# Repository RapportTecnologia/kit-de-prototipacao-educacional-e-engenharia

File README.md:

# Kit Educacional e Prototipação Rapport

* **Versão atual:** 0.6

---

## Visão geral

Este repositório contém o projeto do **Kit Educacional e de Prototipação** da Rapport (Kit Educacional e Prototipação Rapport - KEPR), incluindo a documentação do barramento/modularidade (UCE) e os arquivos de CAD eletrônico em KiCad.

O KEPR é um ecossistema de hardware para **prototipação e aprendizagem** em sistemas embarcados e IoT: uma base modular que permite trocar o microcontrolador sem “quebrar” o restante do projeto, além de integrar **módulos de rede e wireless** (WiFi, Bluetooth e outros) quando essas interfaces não estão disponíveis nativamente no módulo principal.

A proposta é reduzir atrito no desenvolvimento (e no estudo) de firmware e hardware, organizando um padrão de conexão e expansão para acelerar testes, validações e iterações. O projeto busca compatibilidade com famílias como **STM32**, **ESP32**, **AVR (ATtiny/ATmega)** e outros fabricantes.

Este projeto nasce inicialmente com fins **educacionais** (estudos e evolução técnica de Carlos Delfino) e **pode vir a se tornar comercial** no futuro. Ainda assim, o projeto permanece sob a mesma licença para que outras pessoas e empresas possam **usar, adaptar e redistribuir** da forma que desejarem.

**Licença:** Creative Commons **CC BY 4.0** (atribuição). Se você quer colaborar, você pode:

- propor melhorias na arquitetura do barramento e dos módulos;
- revisar esquemáticos/footprints e sugerir boas práticas de layout;
- abrir issues com dúvidas, críticas e ideias;
- enviar PRs com correções, melhorias e novos módulos.

---

## Documentação

- **UCE (placa / barramento):** `UCE_BOARD.md`
- **Changelog:** `CHANGELOG.md`

---

## Projeto KiCad

O projeto principal atualmente está em:

- `kicad/KEPR/`

---

## Repositório Git (origem)

- `git@github.com:RapportTecnologia/kit-de-prototipacao-educacional-e-engenharia.git`

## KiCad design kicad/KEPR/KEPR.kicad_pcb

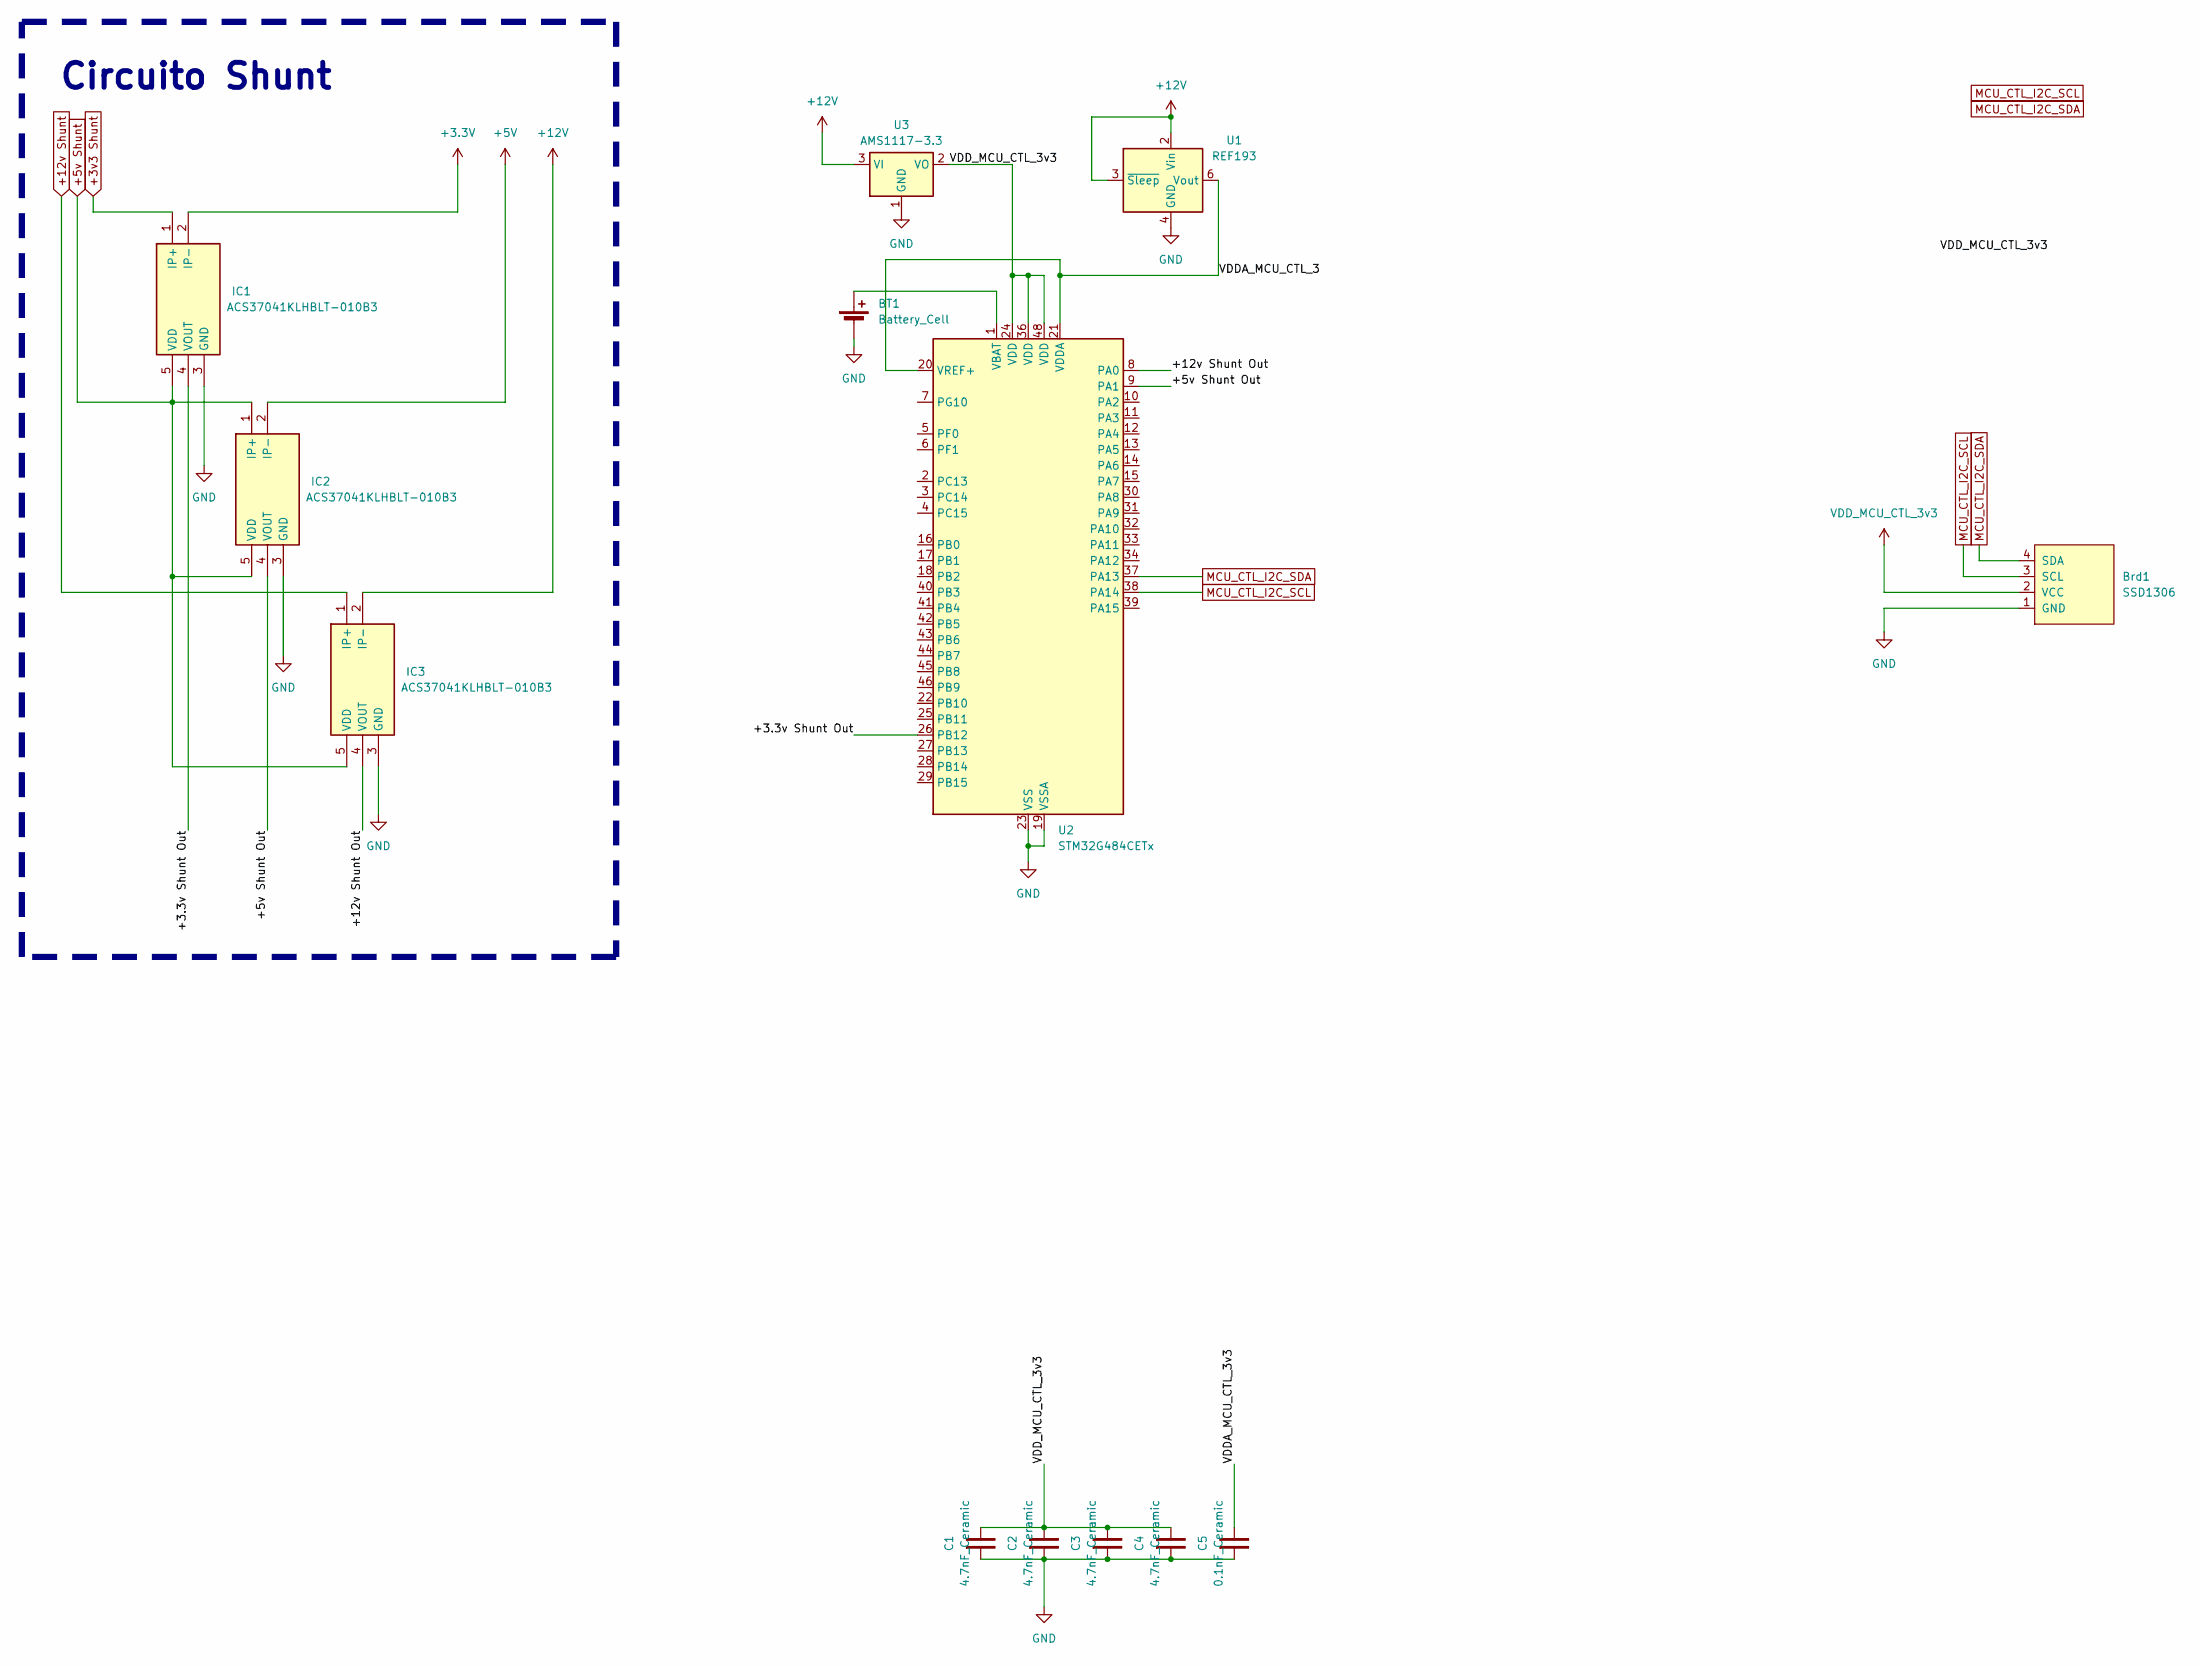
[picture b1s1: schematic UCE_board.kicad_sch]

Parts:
BT1: Battery_Cell; BatteryHolder_Multicomp_BC-2001_1x2032
Brd1: SSD1306; 128x64OLED
C1, C2, C3, C4: 4.7nF_Ceramic; C_0805_2012Metric
C5: 0.1nF_Ceramic; C_0805_2012Metric
IC1, IC2, IC3: ACS37041KLHBLT-010B3; APS12628LLHALTBAP; Manufacturer_Part_Number ACS37041KLHBLT-010B3
U1: REF193; SOIC127P600X175-8N
U2: STM32G484CETx; LQFP-48_7x7mm_P0.5mm
U3: AMS1117-3.3; SOT-223-3_TabPin2

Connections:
+3.3V: IC1.2 (IP-); also elsewhere on the board
+3v3 Shunt: IC1.1 (IP+); also elsewhere on the board
+5V: IC2.2 (IP-); also elsewhere on the board
+5v Shunt: IC1.5 (VDD), IC2.1 (IP+), IC2.5 (VDD), IC3.5 (VDD); also elsewhere on the board
+12V: IC3.2 (IP-), U1.2 (Vin), U1.3 (~Sleep), U3.3 (VI); also elsewhere on the board
+12v Shunt: IC3.1 (IP+); also elsewhere on the board
/UCE board/+3.3v Shunt Out: IC1.4 (VOUT), U2.26 (PB12)
/UCE board/+5v Shunt Out: IC2.4 (VOUT), U2.9 (PA1)
/UCE board/+12v Shunt Out: IC3.4 (VOUT), U2.8 (PA0)
/UCE board/VDDA_MCU_CTL_3: U1.6 (Vout), U2.20 (VREF+), U2.21 (VDDA)
/UCE board/VDDA_MCU_CTL_3v3: C5.2
GND: BT1.2 (-), Brd1.1 (GND), C1.1, C2.1, C3.1, C4.1, C5.1, IC1.3 (GND), IC2.3 (GND), IC3.3 (GND), U1.4 (GND), U2.19 (VSSA), U2.23 (VSS), U2.35 (VSS), U2.47 (VSS), U3.1 (GND); also elsewhere on the board
MCU_CTL_I2C_SCL: Brd1.3 (SCL), U2.38 (PA14); also elsewhere on the board
MCU_CTL_I2C_SDA: Brd1.4 (SDA), U2.37 (PA13); also elsewhere on the board
unnamed: BT1.1 (+), U2.1 (VBAT)
VDD_MCU_CTL_3v3: Brd1.2 (VCC), C1.2, C2.2, C3.2, C4.2, U2.24 (VDD), U2.36 (VDD), U2.48 (VDD), U3.2 (VO)

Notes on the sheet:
Circuito Shunt

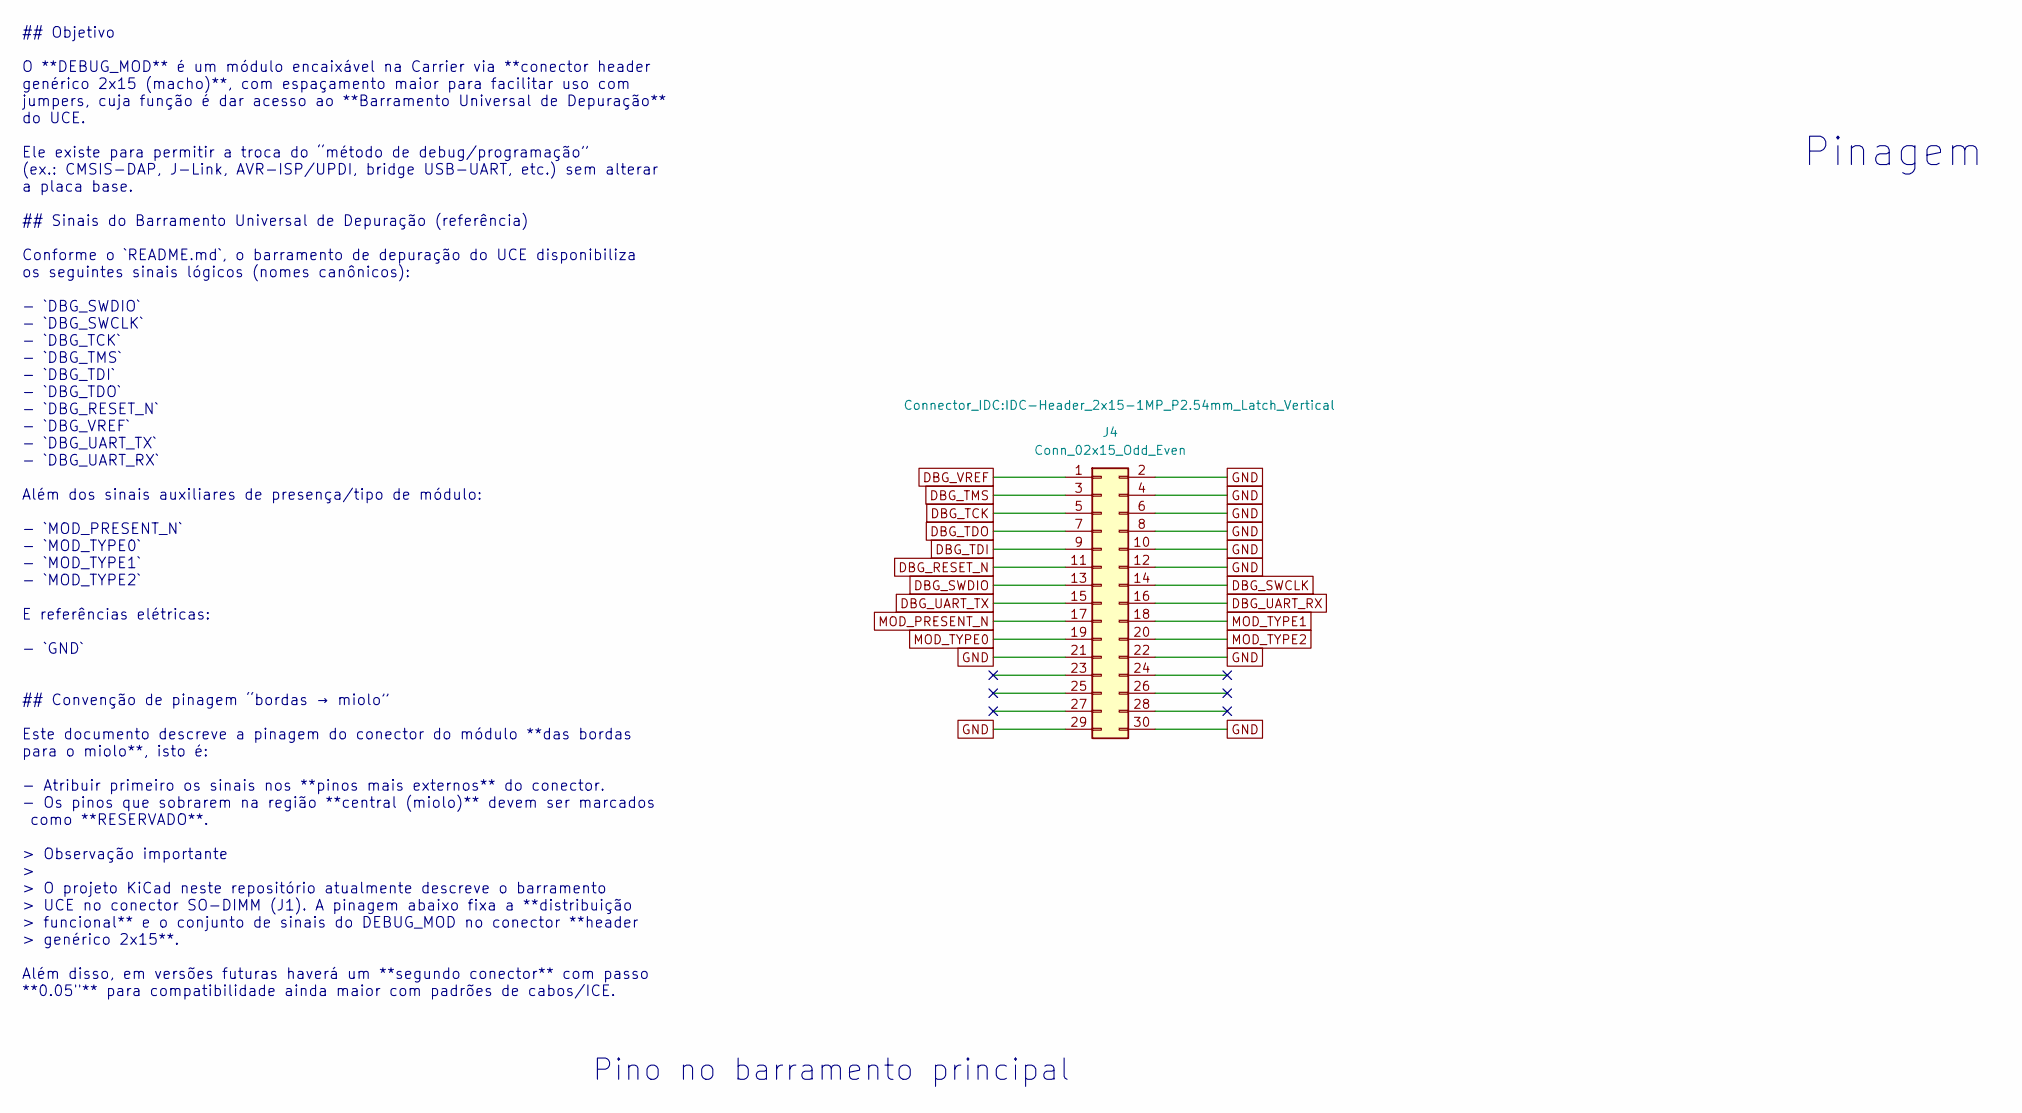
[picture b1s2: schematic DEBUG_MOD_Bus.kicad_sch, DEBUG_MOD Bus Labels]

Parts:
J4: Conn_02x15_Odd_Even; IDC-Header_2x15-1MP_P2.54mm_Latch_Vertical

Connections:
DBG_RESET_N: J4.11; also elsewhere on the board
DBG_SWCLK: J4.14; also elsewhere on the board
DBG_SWDIO: J4.13; also elsewhere on the board
DBG_TCK: J4.5; also elsewhere on the board
DBG_TDI: J4.9; also elsewhere on the board
DBG_TDO: J4.7; also elsewhere on the board
DBG_TMS: J4.3; also elsewhere on the board
DBG_UART_RX: J4.16; also elsewhere on the board
DBG_UART_TX: J4.15; also elsewhere on the board
DBG_VREF: J4.1; also elsewhere on the board
GND: J4.2, J4.4, J4.6, J4.8, J4.10, J4.12, J4.21, J4.22, J4.29, J4.30; also elsewhere on the board
MOD_PRESENT_N: J4.17; also elsewhere on the board
MOD_TYPE0: J4.19; also elsewhere on the board
MOD_TYPE1: J4.18; also elsewhere on the board
MOD_TYPE2: J4.20; also elsewhere on the board

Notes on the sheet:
Pinagem
Pino no barramento principal
## Objetivo O **DEBUG_MOD** é um módulo encaixável na Carrier via **conector header genérico 2x15 (macho)**, com espaçamento maior para facilitar uso com jumpers, cuja função é dar acesso ao **Barramento Universal de Depuração** do UCE. Ele existe para permitir a troca do “método de debug/programaç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

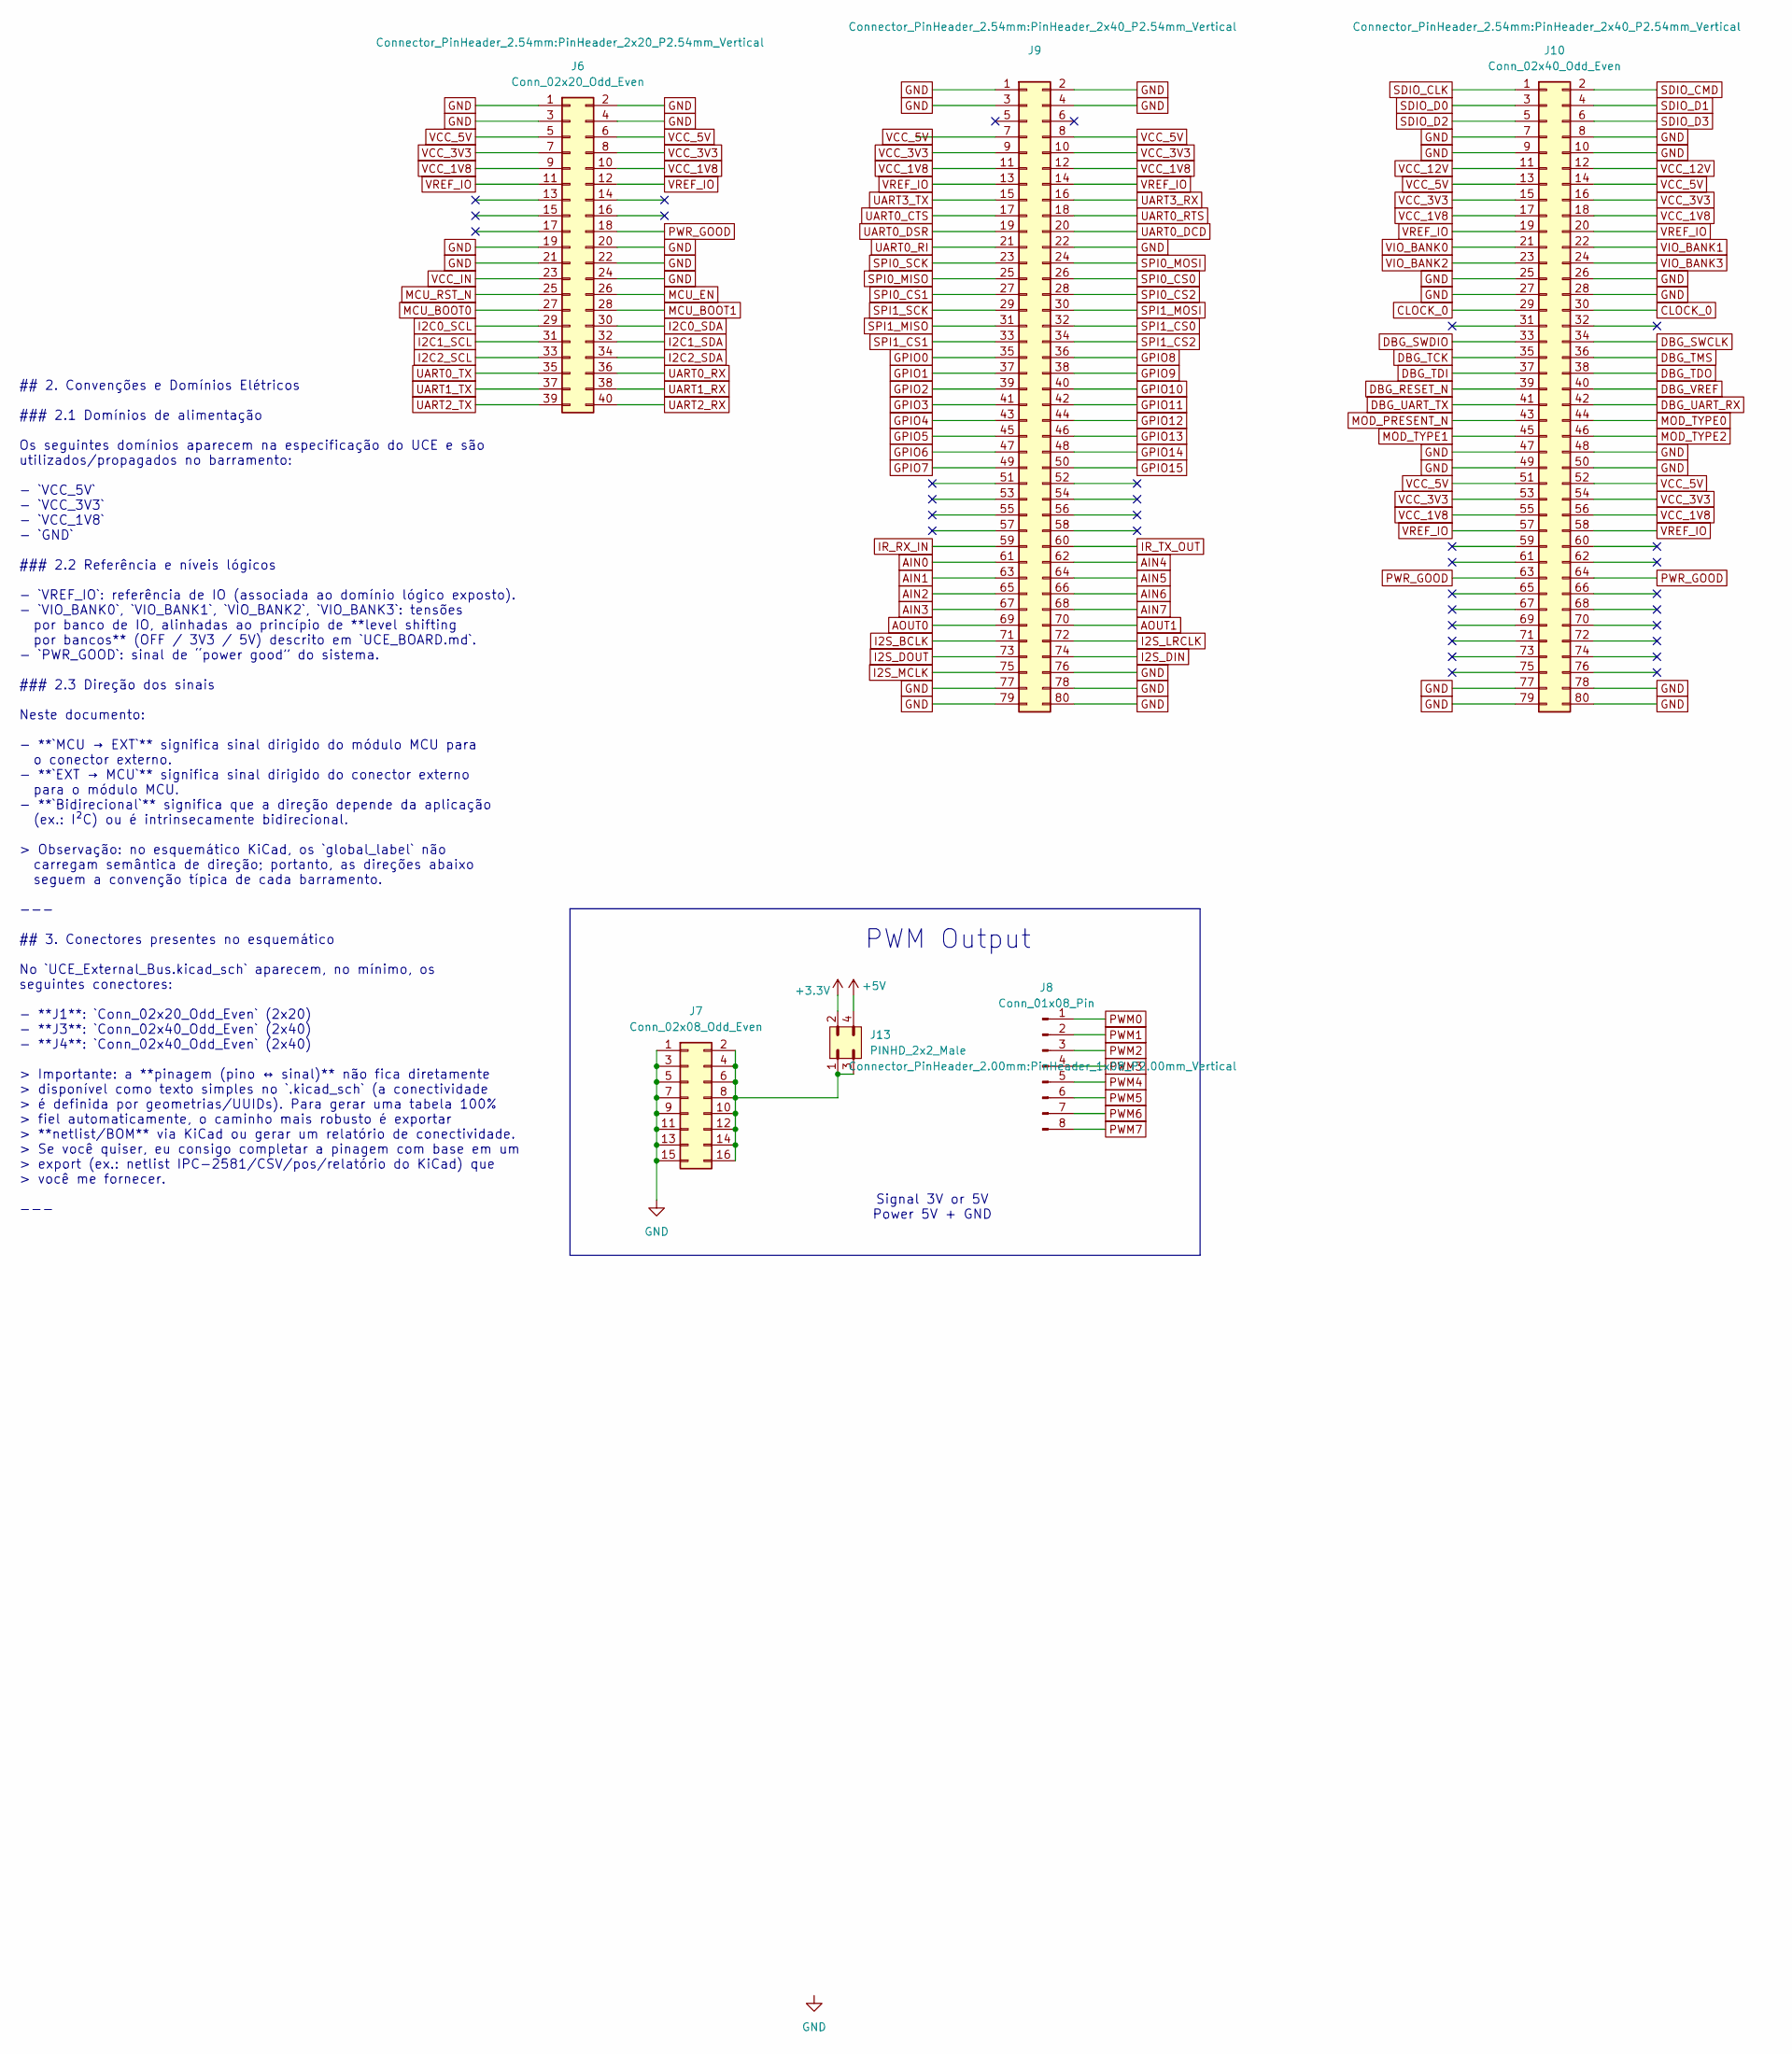
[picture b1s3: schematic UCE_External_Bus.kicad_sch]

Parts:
J6: Conn_02x20_Odd_Even; PinHeader_2x20_P2.54mm_Vertical
J7: Conn_02x08_Odd_Even; PinHeader_2x08_P2.00mm_Vertical
J8: Conn_01x08_Pin; PinHeader_1x08_P2.00mm_Vertical
J9, J10: Conn_02x40_Odd_Even; PinHeader_2x40_P2.54mm_Vertical
J13: PINHD_2x2_Male; PinHeader_2x02_P2.54mm_Vertical

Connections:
+1v8: J6.9, J6.10, J9.11, J9.12, J10.17, J10.18, J10.55, J10.56; also elsewhere on the board
+3.3V: J6.7, J6.8, J9.9, J9.10, J10.15, J10.16, J10.53, J10.54, J13.2; also elsewhere on the board
+5V: J6.5, J6.6, J9.7, J9.8, J10.13, J10.14, J10.51, J10.52, J13.4; also elsewhere on the board
+12V: J10.11, J10.12; also elsewhere on the board
AIN0: J9.61; also elsewhere on the board
AIN1: J9.63; also elsewhere on the board
AIN2: J9.65; also elsewhere on the board
AIN3: J9.67; also elsewhere on the board
AIN4: J9.62; also elsewhere on the board
AIN5: J9.64; also elsewhere on the board
AIN6: J9.66; also elsewhere on the board
AIN7: J9.68; also elsewhere on the board
AOUT0: J9.69; also elsewhere on the board
AOUT1: J9.70; also elsewhere on the board
CLOCK_0: J10.29, J10.30; also elsewhere on the board
DBG_RESET_N: J10.39; also elsewhere on the board
DBG_SWCLK: J10.34; also elsewhere on the board
DBG_SWDIO: J10.33; also elsewhere on the board
DBG_TCK: J10.35; also elsewhere on the board
DBG_TDI: J10.37; also elsewhere on the board
DBG_TDO: J10.38; also elsewhere on the board
DBG_TMS: J10.36; also elsewhere on the board
DBG_UART_RX: J10.42; also elsewhere on the board
DBG_UART_TX: J10.41; also elsewhere on the board
DBG_VREF: J10.40; also elsewhere on the board
GND: J6.1, J6.2, J6.3, J6.4, J6.19, J6.20, J6.21, J6.22, J6.24, J7.1, J7.3, J7.5, J7.7, J7.9, J7.11, J7.13, J7.15, J9.1, J9.2, J9.3, J9.4, J9.22, J9.76, J9.77, J9.78, J9.79, J9.80, J10.7, J10.8, J10.9, J10.10, J10.25, J10.26, J10.27, J10.28, J10.47, J10.48, J10.49, J10.50, J10.77, J10.78, J10.79, J10.80; also elsewhere on the board
GPIO0: J9.35; also elsewhere on the board
GPIO1: J9.37; also elsewhere on the board
GPIO2: J9.39; also elsewhere on the board
GPIO3: J9.41; also elsewhere on the board
GPIO4: J9.43; also elsewhere on the board
GPIO5: J9.45; also elsewhere on the board
GPIO6: J9.47; also elsewhere on the board
GPIO7: J9.49; also elsewhere on the board
GPIO8: J9.36; also elsewhere on the board
GPIO9: J9.38; also elsewhere on the board
GPIO10: J9.40; also elsewhere on the board
GPIO11: J9.42; also elsewhere on the board
GPIO12: J9.44; also elsewhere on the board
GPIO13: J9.46; also elsewhere on the board
GPIO14: J9.48; also elsewhere on the board
GPIO15: J9.50; also elsewhere on the board
I2C0_SCL: J6.29; also elsewhere on the board
I2C0_SDA: J6.30; also elsewhere on the board
I2C1_SCL: J6.31; also elsewhere on the board
I2C1_SDA: J6.32; also elsewhere on the board
I2C2_SCL: J6.33; also elsewhere on the board
I2C2_SDA: J6.34; also elsewhere on the board
I2S_BCLK: J9.71; also elsewhere on the board
I2S_DIN: J9.74; also elsewhere on the board
I2S_DOUT: J9.73; also elsewhere on the board
I2S_LRCLK: J9.72; also elsewhere on the board
I2S_MCLK: J9.75; also elsewhere on the board
IR_RX_IN: J9.59; also elsewhere on the board
IR_TX_OUT: J9.60; also elsewhere on the board
MCU_BOOT0: J6.27; also elsewhere on the board
MCU_BOOT1: J6.28; also elsewhere on the board
MCU_EN: J6.26; also elsewhere on the board
MCU_RST_N: J6.25; also elsewhere on the board
MOD_PRESENT_N: J10.43; also elsewhere on the board
MOD_TYPE0: J10.44; also elsewhere on the board
MOD_TYPE1: J10.45; also elsewhere on the board
MOD_TYPE2: J10.46; also elsewhere on the board
unnamed: J7.2, J7.4, J7.6, J7.8, J7.10, J7.12, J7.14, J7.16, J13.1, J13.3
PWM0: J8.1; also elsewhere on the board
PWM1: J8.2; also elsewhere on the board
PWM2: J8.3; also elsewhere on the board
PWM3: J8.4; also elsewhere on the board
PWM4: J8.5; also elsewhere on the board
PWM5: J8.6; also elsewhere on the board
PWM6: J8.7; also elsewhere on the board
PWM7: J8.8; also elsewhere on the board
PWR_GOOD: J6.18, J10.63, J10.64; also elsewhere on the board
SDIO_CLK: J10.1, J10.3; also elsewhere on the board
SDIO_CMD: J10.2; also elsewhere on the board
SDIO_D1: J10.4; also elsewhere on the board
SDIO_D2: J10.5; also elsewhere on the board
SDIO_D3: J10.6; also elsewhere on the board
SPI0_CS0: J9.26; also elsewhere on the board
SPI0_CS1: J9.27; also elsewhere on the board
SPI0_CS2: J9.28; also elsewhere on the board
SPI0_MISO: J9.25; also elsewhere on the board
SPI0_MOSI: J9.24; also elsewhere on the board
SPI0_SCK: J9.23; also elsewhere on the board
SPI1_CS0: J9.32; also elsewhere on the board
SPI1_CS1: J9.33; also elsewhere on the board
SPI1_CS2: J9.34; also elsewhere on the board
SPI1_MISO: J9.31; also elsewhere on the board
SPI1_MOSI: J9.30; also elsewhere on the board
SPI1_SCK: J9.29; also elsewhere on the board
UART0_CTS: J9.17; also elsewhere on the board
UART0_DCD: J9.20; also elsewhere on the board
UART0_DSR: J9.19; also elsewhere on the board
UART0_RI: J9.21; also elsewhere on the board
UART0_RTS: J9.18; also elsewhere on the board
UART0_RX: J6.36; also elsewhere on the board
UART0_TX: J6.35; also elsewhere on the board
UART1_RX: J6.38; also elsewhere on the board
UART1_TX: J6.37; also elsewhere on the board
UART2_RX: J6.40; also elsewhere on the board
UART2_TX: J6.39; also elsewhere on the board
UART3_RX: J9.16; also elsewhere on the board
UART3_TX: J9.15; also elsewhere on the board
VCC_IN: J6.23; also elsewhere on the board
VIO_BANK0: J10.21
VIO_BANK1: J10.22
VIO_BANK2: J10.23
VIO_BANK3: J10.24
VREF_IO: J6.11, J6.12, J9.13, J9.14, J10.19, J10.20, J10.57, J10.58; also elsewhere on the board

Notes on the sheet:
Signal 3V or 5V Power 5V + GND
## 2. Convenções e Domínios Elétricos ### 2.1 Domínios de alimentação Os seguintes domínios aparecem na especificação do UCE e são utilizados/propagados no barramento: - `VCC_5V` - `VCC_3V3` - `VCC_1V8` - `GND` ### 2.2 Referência e níveis lógicos - `VREF_IO`: referência de IO (associada ao domínio 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
PWM Output

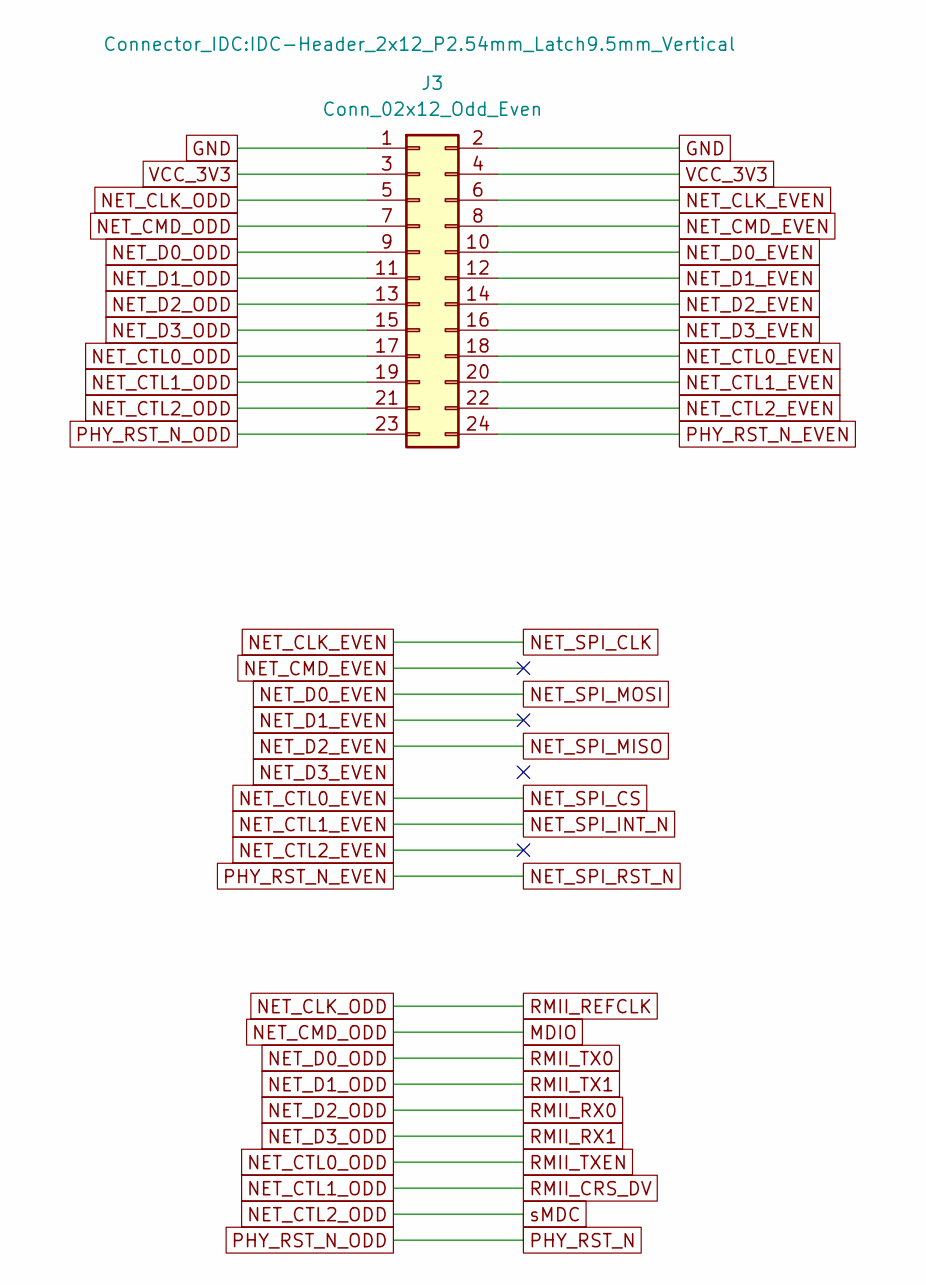
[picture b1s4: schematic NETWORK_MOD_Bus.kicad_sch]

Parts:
J3: Conn_02x12_Odd_Even; IDC-Header_2x12_P2.54mm_Latch9.5mm_Vertical

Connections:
+3.3V: J3.3, J3.4; also elsewhere on the board
GND: J3.1, J3.2; also elsewhere on the board
MDIO: J3.7; also elsewhere on the board
NET_CLK_EVEN: J3.6
NET_CLK_ODD: J3.5; also elsewhere on the board
NET_CMD_EVEN: J3.8
NET_CTL0_EVEN: J3.18; also elsewhere on the board
NET_CTL0_ODD: J3.17; also elsewhere on the board
NET_CTL1_EVEN: J3.20
NET_CTL1_ODD: J3.19; also elsewhere on the board
NET_CTL2_EVEN: J3.22
NET_CTL2_ODD: J3.21, J3.23; also elsewhere on the board
NET_D0_EVEN: J3.10; also elsewhere on the board
NET_D0_ODD: J3.9
NET_D1_EVEN: J3.12
NET_D1_ODD: J3.11
NET_D2_EVEN: J3.14; also elsewhere on the board
NET_D2_ODD: J3.13
NET_D3_EVEN: J3.16
NET_D3_ODD: J3.15
NET_SPI_RST_N: J3.24

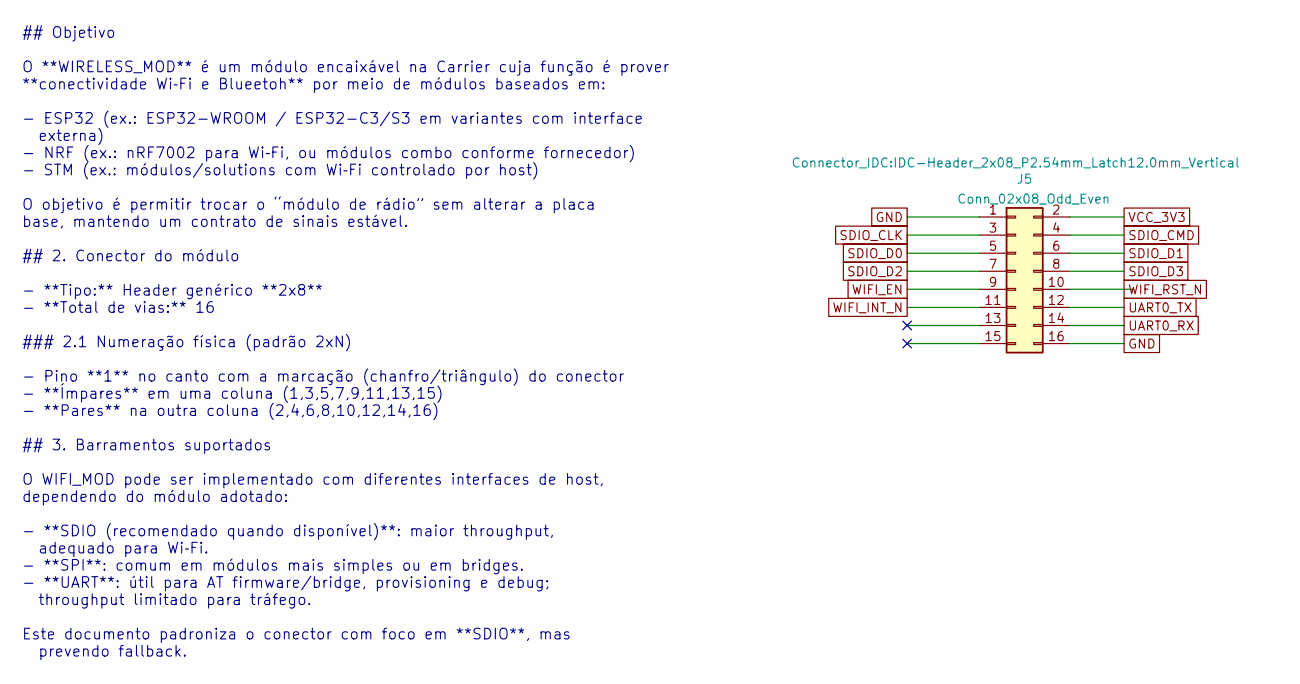
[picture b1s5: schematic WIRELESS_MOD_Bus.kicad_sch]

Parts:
J5: Conn_02x08_Odd_Even; IDC-Header_2x08_P2.54mm_Latch12.0mm_Vertical

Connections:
+3.3V: J5.2; also elsewhere on the board
GND: J5.1, J5.16; also elsewhere on the board
SDIO_CLK: J5.3, J5.5; also elsewhere on the board
SDIO_CMD: J5.4; also elsewhere on the board
SDIO_D1: J5.6; also elsewhere on the board
SDIO_D2: J5.7; also elsewhere on the board
SDIO_D3: J5.8; also elsewhere on the board
UART0_RX: J5.14; also elsewhere on the board
UART0_TX: J5.12; also elsewhere on the board
WIFI_EN: J5.9
WIFI_INT_N: J5.11
WIFI_RST_N: J5.10

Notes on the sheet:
## Objetivo O **WIRELESS_MOD** é um módulo encaixável na Carrier cuja função é prover **conectividade Wi‑Fi e Blueetoh** por meio de módulos baseados em: - ESP32 (ex.: ESP32-WROOM / ESP32-C3/S3 em variantes com interface externa) - NRF (ex.: nRF7002 para Wi‑Fi, ou módulos combo conforme fornecedor)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

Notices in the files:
README.md:
License: CC BY 4.0
